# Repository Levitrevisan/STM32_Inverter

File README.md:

# STM32 Inverter
## Introduction:

University project: Simple micro-inverter using a STM32F103C8.

## Objectives

Generate 3 phase signal through SPWM with 120 degrees of phase diffence. The frequency, phase and amplitude should be controlled through digital buttons.

## Project Roadmap

*  [OK] Be able to generate 6 PWM pulses with different duty cycles
*  [OK] Be able to control duty cycles inside timmed interruption routines
*  [OK] Guarantee that interruption have the timer and counter well adjusted to required time.
*  [OK] Be able to generate 3 SPWM waves with 120 between them
*  [OK] Guarantee that SPWM generated have 120 degrees between them
*  [OK] Control SPWM Amplitude
*  [OK] Implement GPIO input interruption
*  [--] Read Zero Cross signal
*  [OK] Control phase based on Zero Cross signal

## Reference

*  https://www.infineon.com/dgdl/Infineon-IM393-S6E-DS-v02_00-EN.pdf?fileId=5546d462696dbf1201699a9d912478e4 - INFINEON CIPOS datasheet
*  https://www.infineon.com/dgdl/Infineon-AN2016-11_CIPOS_Mini_Inverter_module_reference_board_type1_for_1-shunt_resistor-AN-v01_11-EN.pdf?fileId=5546d462566bd0c7015674af2c20258a - Evaluation board manual (used for "benchmarking" propuses)
*  https://www.st.com/content/ccc/resource/technical/document/reference_manual/59/b9/ba/7f/11/af/43/d5/CD00171190.pdf/files/CD00171190.pdf/jcr:content/translations/en.CD00171190.pdf - STM32 reference manual

## How to use MatLab script to generate SPWM values

The matlab script is used to generate the senoid values that are used as reference for the SPWM generation. You should se the parameters

```
  max_pwm_value = 3550;
  min_pwm_value = 0;
  frequency = 60;
  number_of_points_in_one_cycle = 60;
```

The script will return the int array to be pasted into the MCU code like this:

```
  {1775 ,1961 ,2144 ,2324 ,2497 ,2663 ,2818 ,2963 ,3094 ,3211 ,3312 ,3397 ,3463 ,3511 ,3540 ,3550 ,3540 ,3511 ,3463 ,3397 ,3312 ,3211 ,3094 ,2963 ,2818 ,2663 ,2497 ,2324 ,2144 ,1961 ,1775 ,1589 ,1406 ,1226 ,1053 ,888 ,732 ,587 ,456 ,339 ,238 ,153 ,87 ,39 ,10 ,0 ,10 ,39 ,87 ,153 ,238 ,339 ,456 ,587 ,732 ,887 ,1053 ,1226 ,1406 ,1589 ,}
```
  
It will also return the interuption period in nanoseconds used to control the timed interruption that will update the PWM values to generate the senoid. Lastly, it will show us the stem plot of those points.

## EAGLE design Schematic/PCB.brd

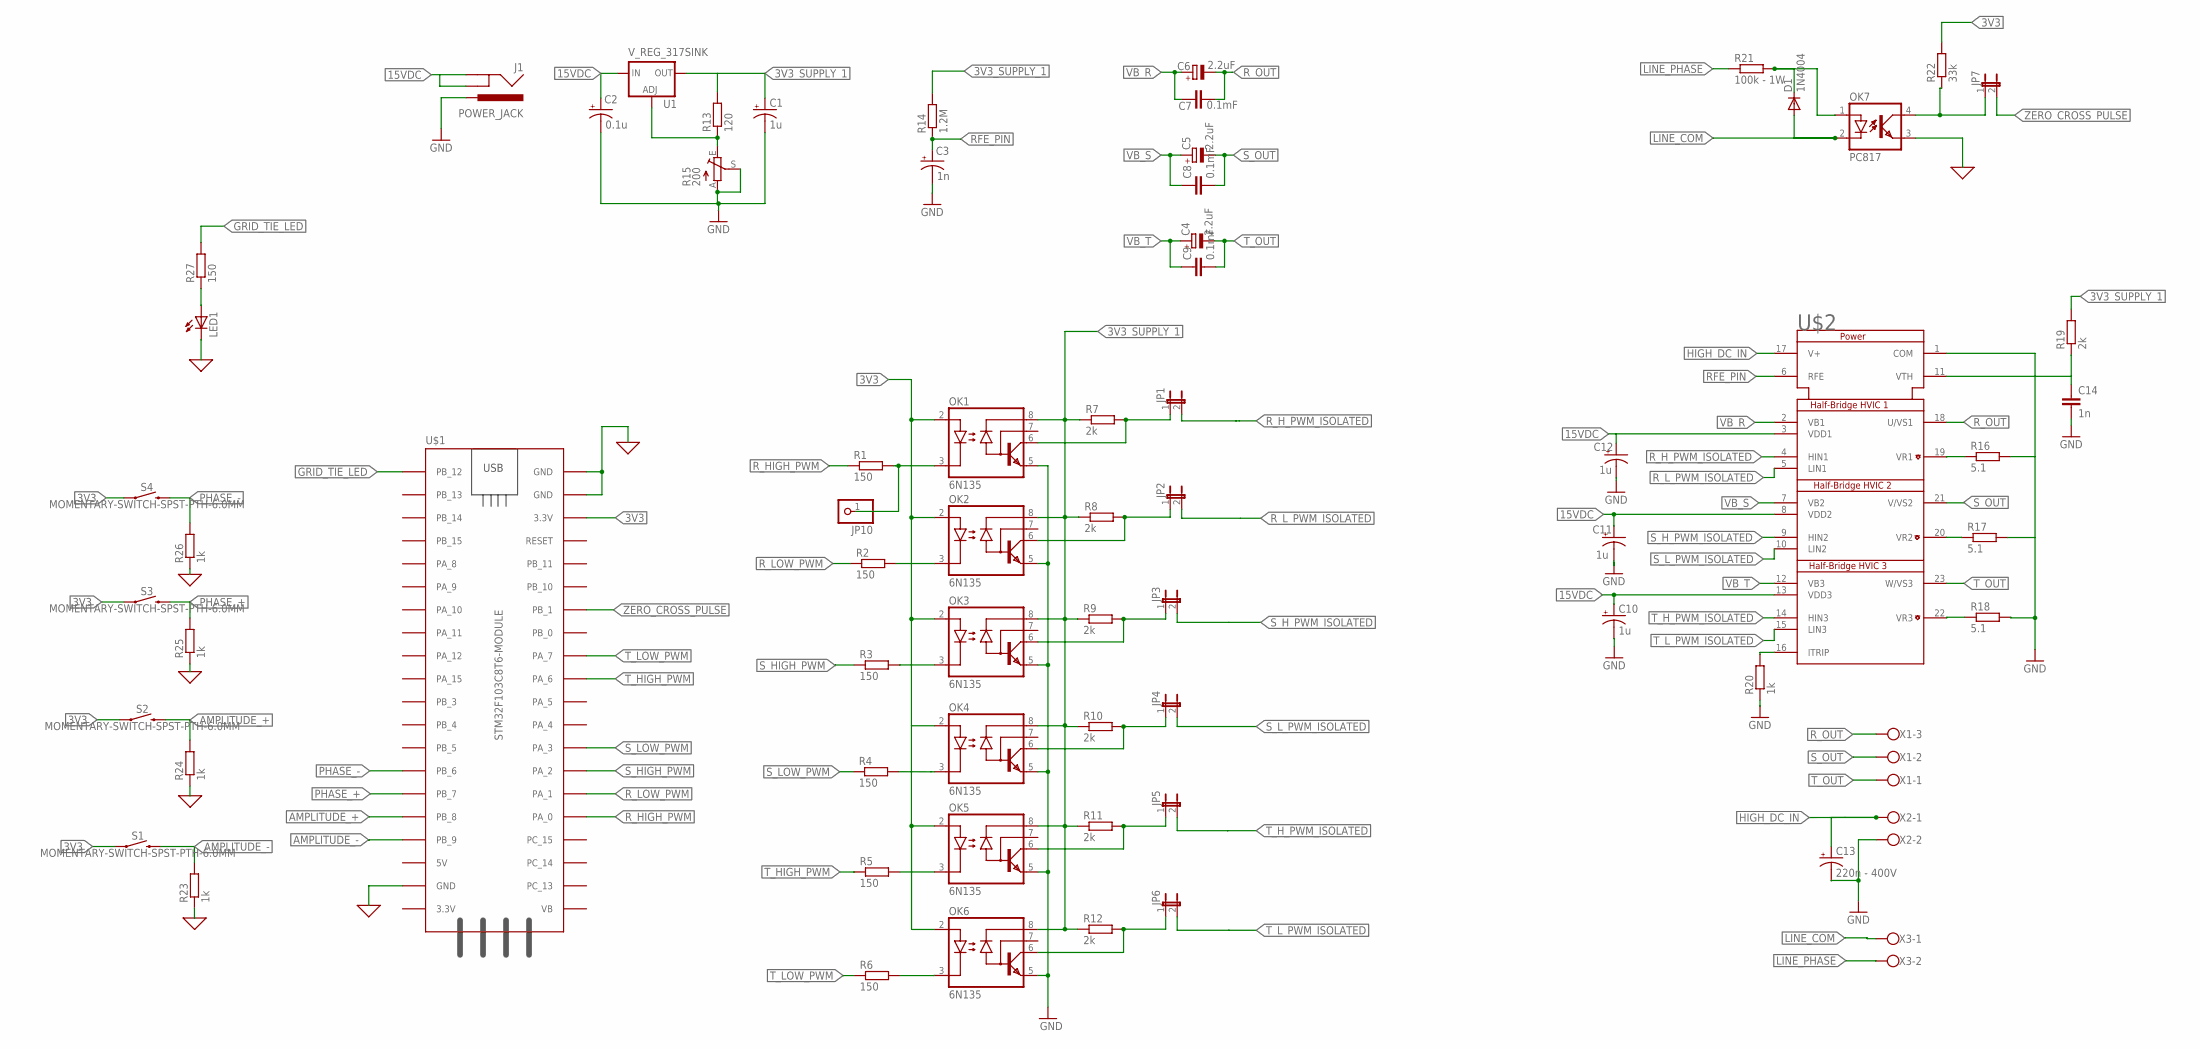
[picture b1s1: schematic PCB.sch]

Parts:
C1, C10, C11, C12: 1u; E5-4
C2: 0.1u; E5-4
C3: 1n; E5-4
C4, C5, C6: 2.2uF; E3,5-8
C7, C8, C9: 0.1mF; C5B5
C13: 220n - 400V; CPOL-RADIAL-5MM-10MM-KIT
C14: 1n; C5B2.5
D1: 1N4004; DO41-10
J1: POWER_JACK; POWER_JACK_PTH
JP1, JP2, JP3, JP4, JP5, JP6, JP7: JP1E; JP1
JP10: PINHD-1X1; 1X01
LED1: LED3MM
OK1, OK2, OK3, OK4, OK5, OK6: 6N135; DIL08
OK7: PC817; DIL04
R1, R2, R3, R4, R5, R6, R27: 150; 0207/10
R7, R8, R9, R10, R11, R12, R19: 2k; 0207/10
R13: 120; 0207/10
R14: 1.2M; 0207/10
R15: 200; RJ9W
R16, R17, R18: 5.1; 0207/10
R20, R23, R24, R25, R26: 1k; 0207/10
R21: 100k - 1W; 0207/10
R22: 33k; 0207/10
S1, S2, S3, S4: MOMENTARY-SWITCH-SPST-PTH-6.0MM; TACTILE_SWITCH_PTH_6.0MM
U1: V_REG_317SINK; TO220-ADJ
U$1: STM32F103C8T6-MODULE
U$2: IM231-M6T2B; DIP-IM231-M6T2B
X1: W237-103
X2, X3: W237-102

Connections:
0: LED1.K (C), OK7.3 (EMIT), R23.1, R24.1, R25.1, R26.1, U$1.GND_1 (GND), U$1.GND_2 (GND), U$1.GND_3 (GND)
3V3: OK1.2 (A), OK2.2 (A), OK3.2 (A), OK4.2 (A), OK5.2 (A), OK6.2 (A), R22.2, S1.1, S2.1, S3.1, S4.1, U$1.3.3V_2 (3.3V)
3V3_SUPPLY_1: C1.+, OK1.8 (VCC), OK2.8 (VCC), OK3.8 (VCC), OK4.8 (VCC), OK5.8 (VCC), OK6.8 (VCC), R7.1, R8.1, R9.1, R10.1, R11.1, R12.1, R13.2, R14.2, R19.2, U1.OUT
15VDC: C2.+, C10.+, C11.+, C12.+, J1.GND, J1.GNDBREAK, U1.IN, U$2.3 (VDD1), U$2.8 (VDD2), U$2.13 (VDD3)
AMPLITUDE_+: R24.2, S2.3 (2), U$1.PB_8
AMPLITUDE_-: R23.2, S1.3 (2), U$1.PB_9
GND: C1.-, C2.-, C3.-, C10.-, C11.-, C12.-, C13.-, C14.2, J1.PWR, OK1.5 (GND), OK2.5 (GND), OK3.5 (GND), OK4.5 (GND), OK5.5 (GND), OK6.5 (GND), R15.A, R15.S, R16.2, R17.2, R18.2, R20.1, U$2.1 (COM), X2.2
GRID_TIE_LED: R27.2, U$1.PB_12
HIGH_DC_IN: C13.+, U$2.17 (V+), X2.1
LINE_COM: D1.A, OK7.2 (C), X3.1
LINE_PHASE: R21.1, X3.2
unnamed: JP10.1, OK1.3 (C), R1.2
unnamed: OK2.3 (C), R2.2
unnamed: OK3.3 (C), R3.2
unnamed: OK4.3 (C), R4.2
unnamed: OK5.3 (C), R5.2
unnamed: OK6.3 (C), R6.2
unnamed: R13.1, R15.E, U1.ADJ
unnamed: R20.2, U$2.16 (ITRIP)
unnamed: R16.1, U$2.19 (VR1)
unnamed: R17.1, U$2.20 (VR2)
unnamed: R18.1, U$2.22 (VR3)
unnamed: D1.C, OK7.1 (A), R21.2
unnamed: C14.1, R19.1, U$2.11 (VTH)
unnamed: JP7.1, OK7.4 (COL), R22.1
unnamed: LED1.A, R27.1
PHASE_+: R25.2, S3.3 (2), U$1.PB_7
PHASE_-: R26.2, S4.3 (2), U$1.PB_6
RFE_PIN: C3.+, R14.1, U$2.6 (RFE)
R_HIGH_PWM: R1.1, U$1.PA_0
R_HIGH_PWM_ISOLATED: JP1.1, OK1.6 (VO), R7.2
R_H_PWM_ISOLATED: JP1.2, U$2.4 (HIN1)
R_LOW_PWM: R2.1, U$1.PA_1
R_LOW_PWM_ISOLATED: JP2.1, OK2.6 (VO), R8.2
R_L_PWM_ISOLATED: JP2.2, U$2.5 (LIN1)
R_OUT: C6.-, C7.2, U$2.18 (U/VS1), X1.3
S_HIGH_PWM: R3.1, U$1.PA_2
S_HIGH_PWM_ISOLATED: JP3.1, OK3.6 (VO), R9.2
S_H_PWM_ISOLATED: JP3.2, U$2.9 (HIN2)
S_LOW_PWM: R4.1, U$1.PA_3
S_LOW_PWM_ISOLATED: JP4.1, OK4.6 (VO), R10.2
S_L_PWM_ISOLATED: JP4.2, U$2.10 (LIN2)
S_OUT: C5.-, C8.2, U$2.21 (V/VS2), X1.2
T_HIGH_PWM: R5.1, U$1.PA_6
T_HIGH_PWM_ISOLATED: JP5.1, OK5.6 (VO), R11.2
T_H_PWM_ISOLATED: JP5.2, U$2.14 (HIN3)
T_LOW_PWM: R6.1, U$1.PA_7
T_LOW_PWM_ISOLATED: JP6.1, OK6.6 (VO), R12.2
T_L_PWM_ISOLATED: JP6.2, U$2.15 (LIN3)
T_OUT: C4.-, C9.2, U$2.23 (W/VS3), X1.1
VB_R: C6.+, C7.1, U$2.2 (VB1)
VB_S: C5.+, C8.1, U$2.7 (VB2)
VB_T: C4.+, C9.1, U$2.12 (VB3)
ZERO_CROSS_PULSE: JP7.2, U$1.PB_1

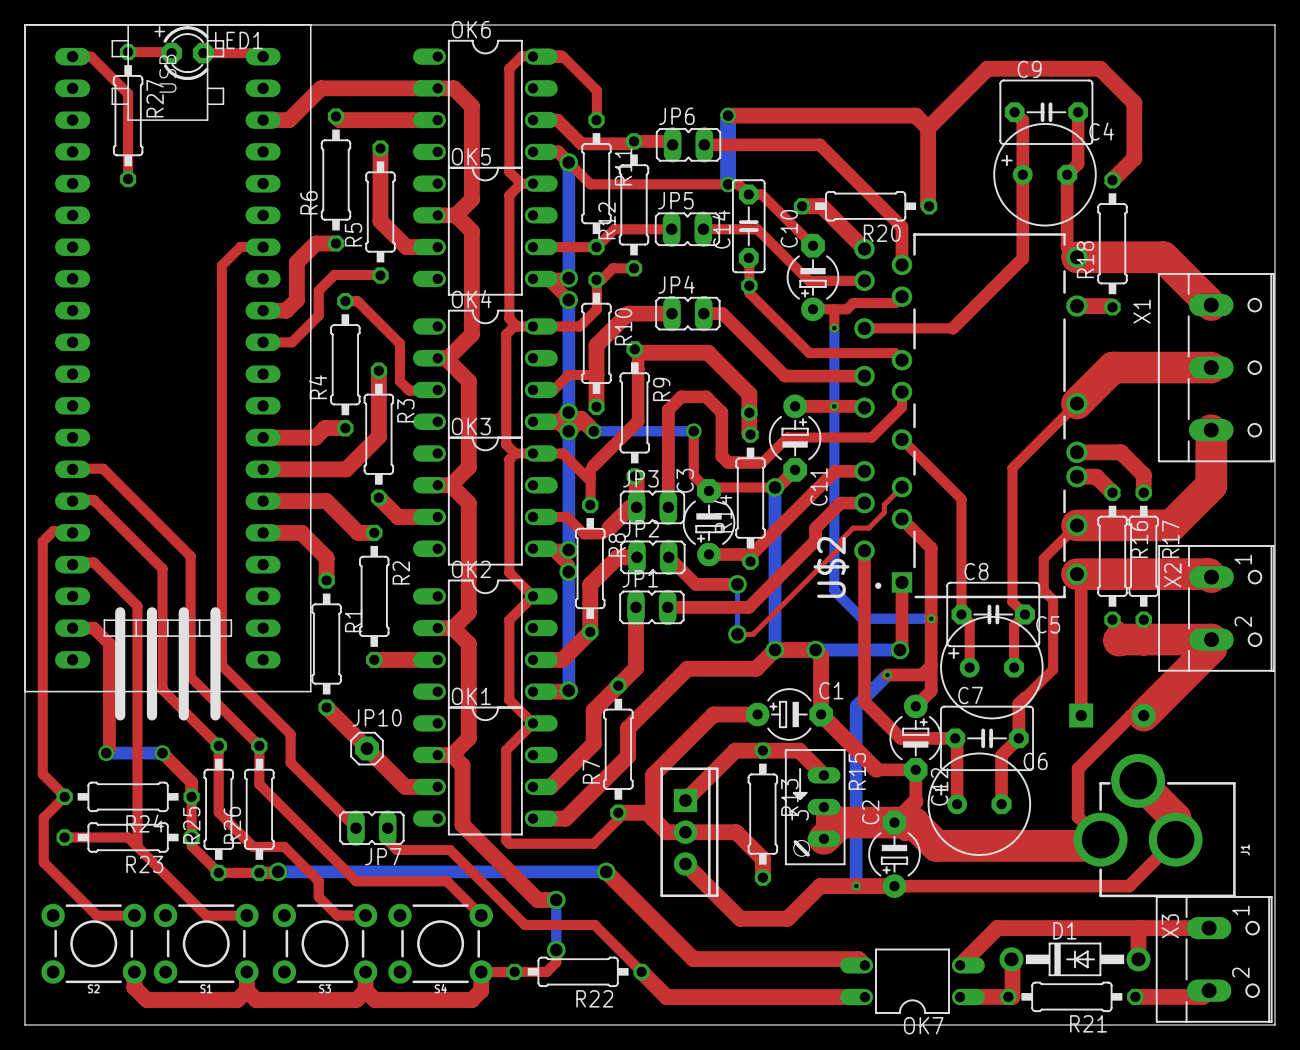
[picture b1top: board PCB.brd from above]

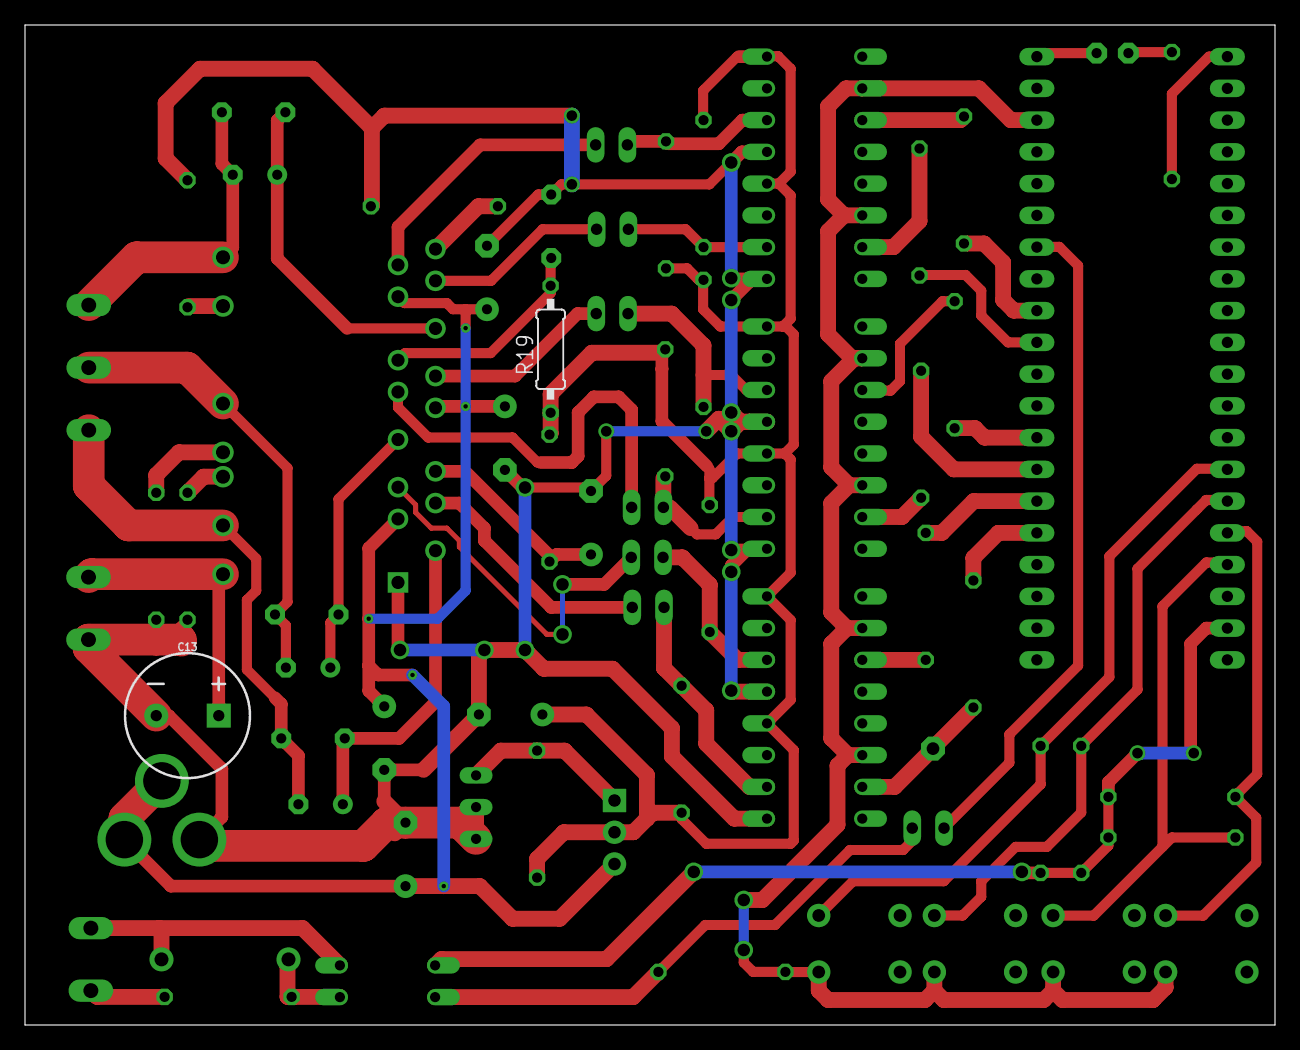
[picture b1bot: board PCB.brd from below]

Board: 2 copper layers, 100.0 x 80.0 mm, 69 parts (2 on the bottom side), 54 nets.

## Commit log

2019-06-28 attached interruption on timer 4
2019-06-28 attatched interrupt on timer 4 each 1ms
2019-07-03 genereted SPWM on phase R
2019-07-05 added 3 phase pwm update functions
2019-07-05 random changes in keil project files
2019-07-05 added MatLab script topic
2019-07-09 added interruption on pin PB1
2019-07-09 adjusted interrupt timming to generate solid 60Hz SPWM
2019-07-13 added references and Matlab script explanation
2019-07-13 updated code syntax
2019-07-13 added image file to matlab script and changed some components values on eagle
2019-07-14 implemented buttons (not phase control yet) and updated schematic
2019-07-14 updated project roadmap
2019-07-15 added schematics
2019-07-15 added protection diode on zero cross detector
2019-07-15 adicionei o relatório do projeto
2019-07-18 updated progress
2019-07-18 finished PCB and corrected schematic
2019-07-18 added schematic pdf

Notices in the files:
parts and their libraries:
SparkFun-IC-Power: Licensing: Creative Commons ShareAlike 4.0 International - https://creativecommons.org/licenses/by-sa/4.0
